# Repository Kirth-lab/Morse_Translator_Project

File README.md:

# Morse Translator Project

Made by melluche and Kirth-lab, 1st-year students at ENSEA.
The Morse Translator project allows you to translate a Morse coded message by typing your message in the keypads. It also works in the opposite way : you can code your message in Morse language, and the alphabet coded message will show in the screen. 

In the repository, you may find all the PCB files, code and datasheets. We also left the 3D model of our case, where you can put your PCB, and fix the screen on the top of it. Feel free to explore it.

> At this state of the project, we don't know if the PCB works. We will keep you updated.

### Objectives :
- Translate a Morse coded message to an alphabet coded message by typing the touch "." and "-" on the keypads. After coding, the message will be shown on the screen and you will be able to read it.
- Translate an alphabet coded message to a Morse coded message using the keypads. After typing, a buzzer will play the *bips* of the message, and a LED will blink at the same time.

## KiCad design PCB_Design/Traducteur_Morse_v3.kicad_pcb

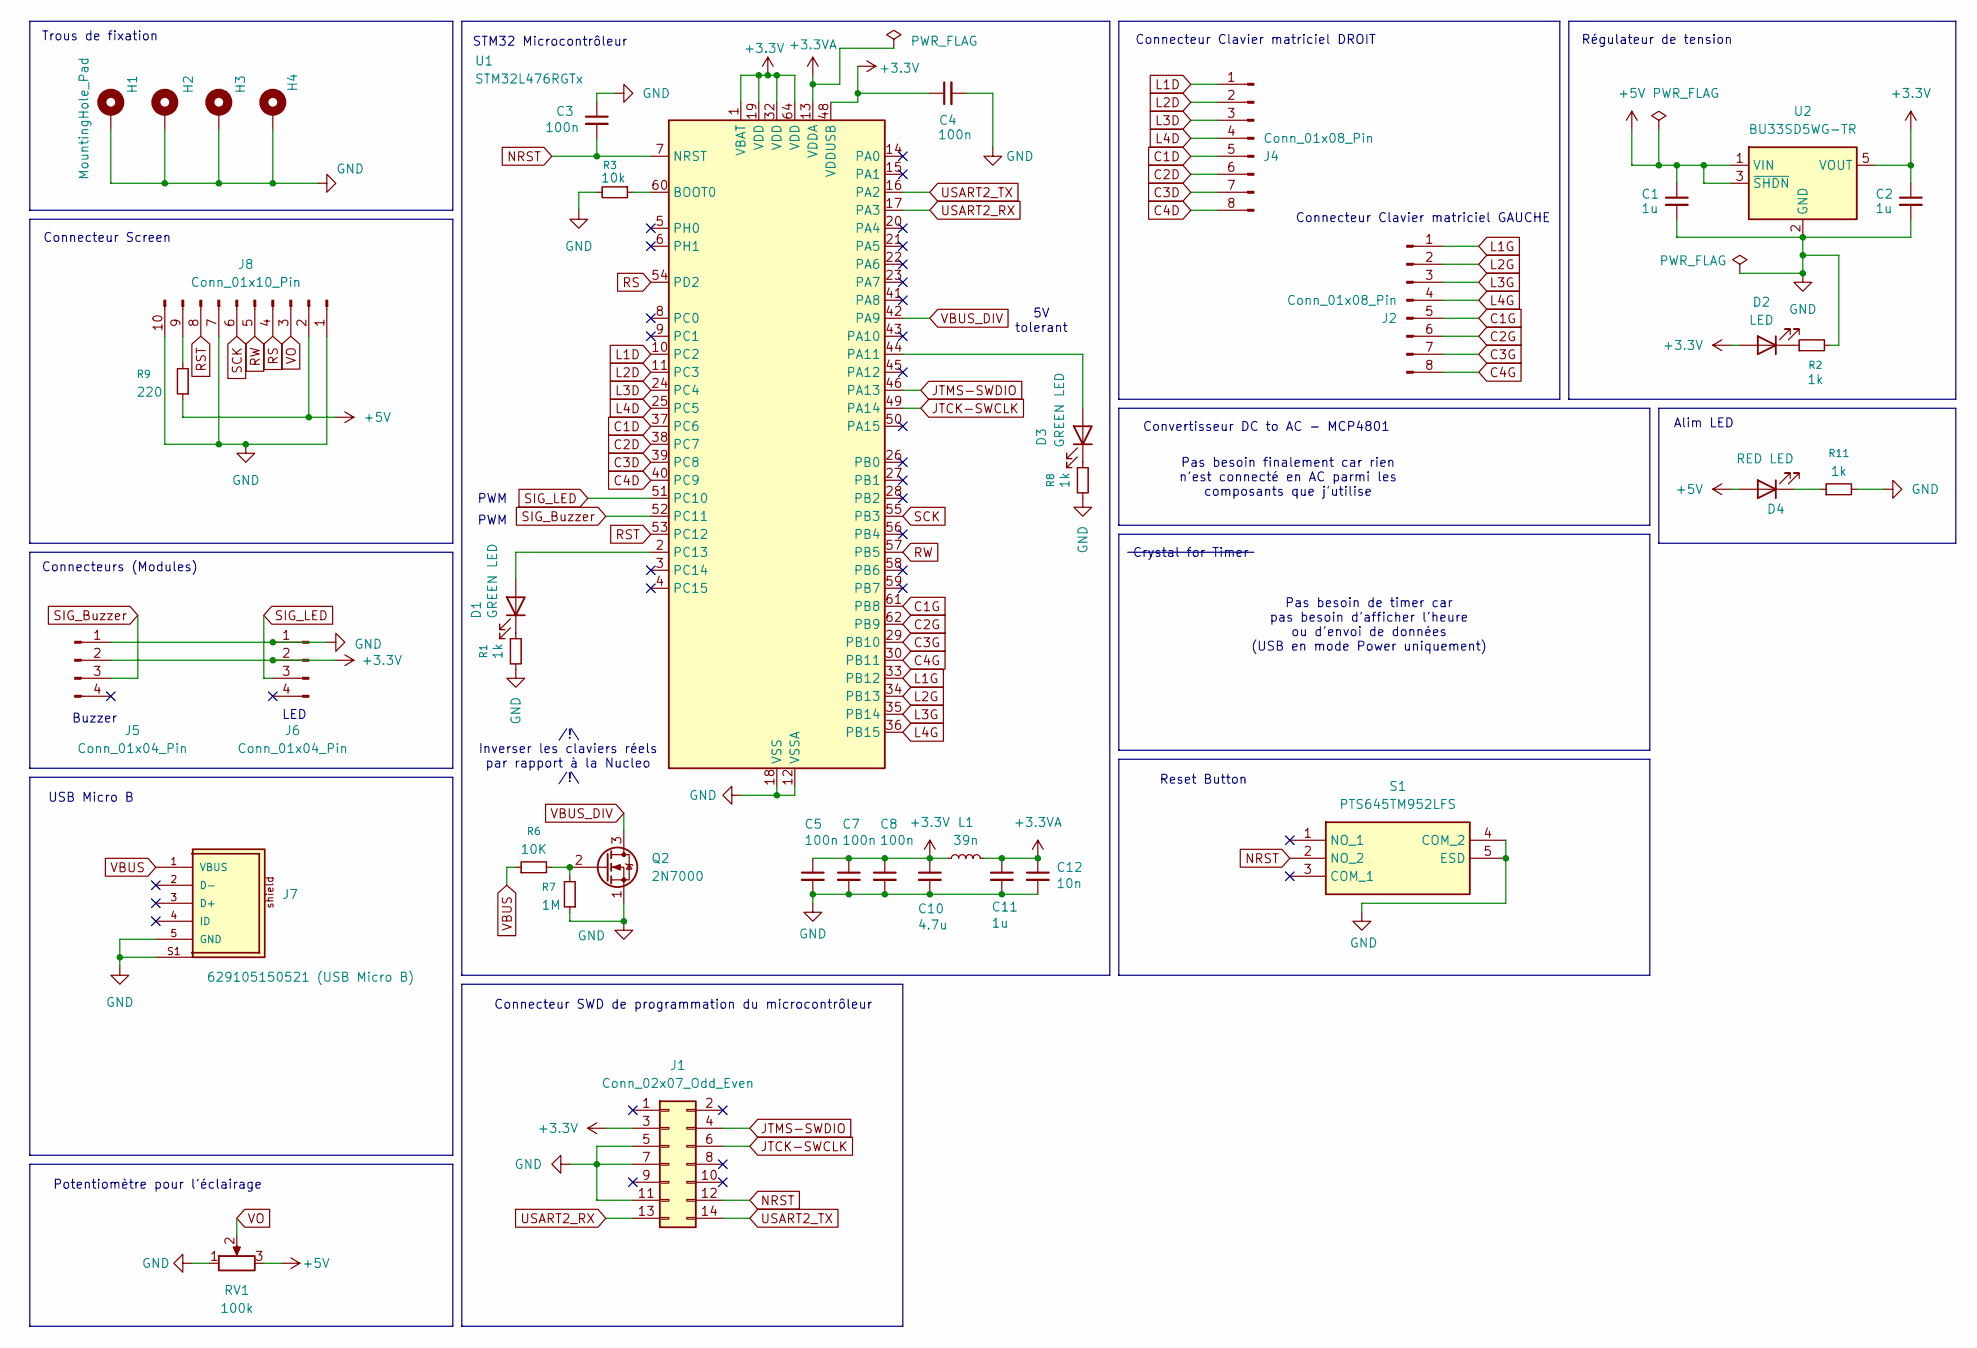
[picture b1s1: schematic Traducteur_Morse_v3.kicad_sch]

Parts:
C1, C2, C11: 1u; C_0805_2012Metric_Pad1.18x1.45mm_HandSolder
C3, C4, C5, C7, C8: 100n; C_0805_2012Metric_Pad1.18x1.45mm_HandSolder
C10: 4.7u; C_0805_2012Metric_Pad1.18x1.45mm_HandSolder
C12: 10n; C_0805_2012Metric_Pad1.18x1.45mm_HandSolder
D1, D3: GREEN LED; LED_0805_2012Metric_Pad1.15x1.40mm_HandSolder
D2: LED; LED_0805_2012Metric_Pad1.15x1.40mm_HandSolder
D4: RED LED; LED_0805_2012Metric_Pad1.15x1.40mm_HandSolder
H1, H2, H3, H4: MountingHole_Pad; MountingHole_3.2mm_M3_DIN965_Pad
J1: Conn_02x07_Odd_Even; PinHeader_2x07_P1.27mm_Vertical_SMD
J2, J4: Conn_01x08_Pin; PinHeader_1x08_P2.54mm_Vertical
J5, J6: Conn_01x04_Pin; JST_XH_B4B-XH-A_1x04_P2.50mm_Vertical
J7: 629105150521 (USB Micro B); 629105150521
J8: Conn_01x10_Pin; PinHeader_1x10_P2.54mm_Vertical
L1: 39n; L_0805_2012Metric_Pad1.05x1.20mm_HandSolder
Q2: 2N7000; TO-92_Inline
R1, R2, R8, R11: 1k; R_0805_2012Metric_Pad1.20x1.40mm_HandSolder
R3: 10k; R_0805_2012Metric_Pad1.20x1.40mm_HandSolder
R6: 10K; R_0805_2012Metric_Pad1.20x1.40mm_HandSolder
R7: 1M; R_0805_2012Metric_Pad1.20x1.40mm_HandSolder
R9: 220; R_0805_2012Metric_Pad1.20x1.40mm_HandSolder
RV1: 100k; Potentiometer_Vishay_T93XA_Horizontal
S1: PTS645TM952LFS; Manufacturer_Part_Number PTS645TM952LFS; Mouser Part Number 611-PTS645TM95LFS
U1: STM32L476RGTx; LQFP-64_10x10mm_P0.5mm
U2: BU33SD5WG-TR; SOT-23-5

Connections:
+3.3V: C2.1, C4.1, C5.1, C7.1, C8.1, C10.1, D2.2 (A), J1.3, J5.2, J6.2, L1.1, U1.1 (VBAT), U1.19 (VDD), U1.32 (VDD), U1.48 (VDDUSB), U1.64 (VDD), U2.5 (VOUT)
+3.3VA: C11.1, C12.1, L1.2, U1.13 (VDDA)
+5V: C1.1, D4.2 (A), J8.2, R9.1, RV1.3, U2.1 (VIN), U2.3 (~SHDN)
C1D: J4.5, U1.37 (PC6)
C1G: J2.5, U1.61 (PB8)
C2D: J4.6, U1.38 (PC7)
C2G: J2.6, U1.62 (PB9)
C3D: J4.7, U1.39 (PC8)
C3G: J2.7, U1.29 (PB10)
C4D: J4.8, U1.40 (PC9)
C4G: J2.8, U1.30 (PB11)
GND: C1.2, C2.2, C3.1, C4.2, C5.2, C7.2, C8.2, C10.2, C11.2, C12.2, H1.1, H2.1, H3.1, H4.1, J1.5, J1.7, J1.11, J5.1, J6.1, J7.5 (GND), J7.S1, J7.S2, J7.S3, J7.S4, J8.1, J8.7, J8.10, Q2.1 (S), R1.2, R2.2, R3.2, R7.1, R8.2, R11.2, RV1.1, S1.4 (COM_2), S1.5 (ESD), U1.12 (VSSA), U1.18 (VSS), U1.31 (VSS), U1.47 (VSS), U1.63 (VSS), U2.2 (GND); also elsewhere on the board
JTCK-SWCLK: J1.6, U1.49 (PA14)
JTMS-SWDIO: J1.4, U1.46 (PA13)
L1D: J4.1, U1.10 (PC2)
L1G: J2.1, U1.33 (PB12)
L2D: J4.2, U1.11 (PC3)
L2G: J2.2, U1.34 (PB13)
L3D: J4.3, U1.24 (PC4)
L3G: J2.3, U1.35 (PB14)
L4D: J4.4, U1.25 (PC5)
L4G: J2.4, U1.36 (PB15)
NRST: C3.2, J1.12, S1.2 (NO_2), U1.7 (NRST); also elsewhere on the board
unnamed: D1.2 (A), U1.2 (PC13)
unnamed: D1.1 (K), R1.1
unnamed: D2.1 (K), R2.1
unnamed: D3.2 (A), U1.44 (PA11)
unnamed: D3.1 (K), R8.1
unnamed: D4.1 (K), R11.1
unnamed: J8.9, R9.2
unnamed: Q2.2 (G), R6.2, R7.2
unnamed: R3.1, U1.60 (BOOT0)
RS: J8.4, U1.54 (PD2)
RST: J8.8, U1.53 (PC12)
RW: J8.5, U1.57 (PB5)
SCK: J8.6, U1.55 (PB3)
SIG_Buzzer: J5.3, U1.52 (PC11)
SIG_LED: J6.3, U1.51 (PC10)
USART2_RX: J1.13, U1.17 (PA3)
USART2_TX: J1.14, U1.16 (PA2)
VBUS: J7.1 (VBUS), R6.1
VBUS_DIV: Q2.3 (D), U1.42 (PA9)
VO: J8.3, RV1.2

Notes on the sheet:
Connecteur Clavier matriciel DROIT
Crystal for Timer
/!\ Inverser les claviers réels par rapport à la Nucleo /!\
Régulateur de tension
PWM
Reset Button
LED
Connecteur Screen
Connecteurs (Modules)
Pas besoin finalement car rien n'est connecté en AC parmi les composants que j'utilise
Connecteur Clavier matriciel GAUCHE
Pas besoin de timer car pas besoin d'afficher l'heure ou d'envoi de données (USB en mode Power uniquement)
Trous de fixation
Alim LED
5V tolerant
Convertisseur DC to AC - MCP4801
USB Micro B
Buzzer
STM32 Microcontrôleur
Connecteur SWD de programmation du microcontrôleur
Potentiomètre pour l'éclairage

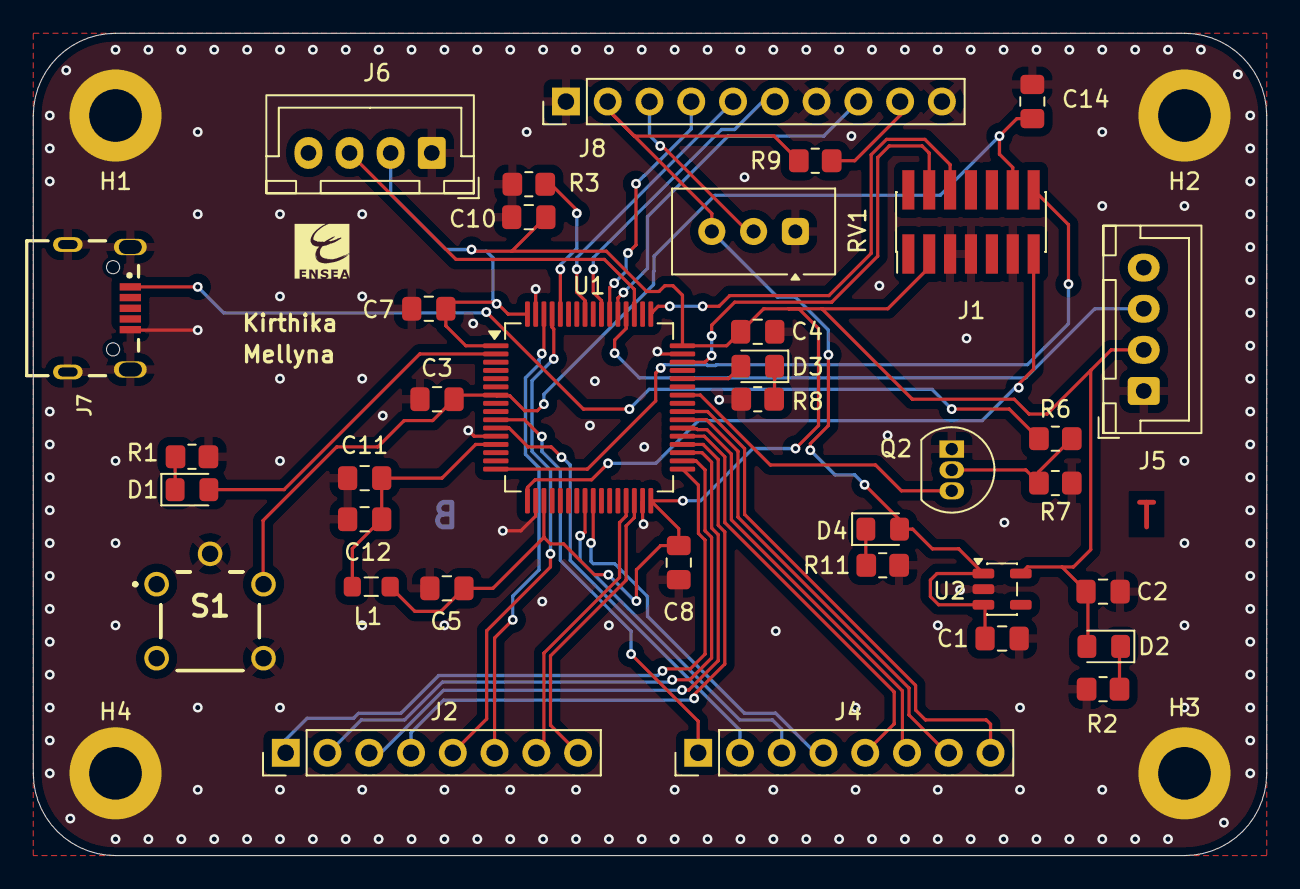
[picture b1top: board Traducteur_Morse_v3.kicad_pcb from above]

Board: 2 copper layers, 75.0 x 50.0 mm, 40 parts (0 on the bottom side), 43 nets.

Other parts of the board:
C14: 100n; C_0805_2012Metric_Pad1.18x1.45mm_HandSolder

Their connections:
GND: C14.2; also elsewhere on the board
NRST: C14.1; also elsewhere on the board

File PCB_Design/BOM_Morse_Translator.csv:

"Id";"Designator";"Footprint";"Quantity";"Designation";"Supplier and ref";
1;"C12";"C_0805_2012Metric_Pad1.18x1.45mm_HandSolder";1;"10n";;;
2;"R6";"R_0805_2012Metric_Pad1.20x1.40mm_HandSolder";1;"10K";;;
3;"J7";"629105150521";1;"629105150521 (USB Micro B)";;;
4;"J5,J6";"JST_XH_B4B-XH-A_1x04_P2.50mm_Vertical";2;"Conn_01x04_Pin";;;
5;"C14,C5,C4,C8,C7,C3";"C_0805_2012Metric_Pad1.18x1.45mm_HandSolder";6;"100n";;;
6;"J8";"PinHeader_1x10_P2.54mm_Vertical";1;"Conn_01x10_Pin";;;
7;"D1,D3";"LED_0805_2012Metric_Pad1.15x1.40mm_HandSolder";2;"GREEN LED";;;
8;"R7";"R_0805_2012Metric_Pad1.20x1.40mm_HandSolder";1;"1M";;;
9;"C2,C1,C11";"C_0805_2012Metric_Pad1.18x1.45mm_HandSolder";3;"1u";;;
10;"J4,J2";"PinHeader_1x08_P2.54mm_Vertical";2;"Conn_01x08_Pin";;;
11;"U1";"LQFP-64_10x10mm_P0.5mm";1;"STM32L476RGTx";;;
12;"D2";"LED_0805_2012Metric_Pad1.15x1.40mm_HandSolder";1;"LED";;;
13;"R3";"R_0805_2012Metric_Pad1.20x1.40mm_HandSolder";1;"10k";;;
14;"D4";"LED_0805_2012Metric_Pad1.15x1.40mm_HandSolder";1;"RED LED";;;
15;"R8,R11,R1,R2";"R_0805_2012Metric_Pad1.20x1.40mm_HandSolder";4;"1k";;;
16;"RV1";"Potentiometer_Vishay_T93XA_Horizontal";1;"100k";;;
17;"C10";"C_0805_2012Metric_Pad1.18x1.45mm_HandSolder";1;"4.7u";;;
18;"L1";"L_0805_2012Metric_Pad1.05x1.20mm_HandSolder";1;"39n";;;
19;"R9";"R_0805_2012Metric_Pad1.20x1.40mm_HandSolder";1;"220";;;
20;"U2";"SOT-23-5";1;"BU33SD5WG-TR";;;
21;"Q2";"TO-92_Inline";1;"2N7000";;;
22;"J1";"PinHeader_2x07_P1.27mm_Vertical_SMD";1;"Conn_02x07_Odd_Even";;;
23;"S1";"PTS645TM952LFS";1;"PTS645TM952LFS";;;

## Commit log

2026-05-14 Revise README for Morse Translator Project
    Updated project description and objectives for clarity.
2026-05-14 Added files
2026-05-14 Modified 3D PCB files
